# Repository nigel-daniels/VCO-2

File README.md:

# VCO 2

This VCO based on the work of  LMNC [performance VCO](https://www.lookmumnocomputer.com/1222-performance-vco). I've swapped out the built in tuner for a sine wave generator based on the Henry Thomas design. I also expanded the octave range by one and enabled hard/soft sync selection. Finally I've set the gain on the output Op-Amps so that everything is around 9-10V out. Why drop the tuner? Well, I'm unlikely to go performing and I was thinking I'll just build a single tuning module to take advantage of the control panel trim pots.

This module is verified and you can check it out working [here](https://bleepsnbloops.com/?p=62). The module draws +12V 48mA and -12V 21mA (+/-5mA). 

There are a couple of folders included, these contain footprints I used for the switches, import these as project specific items. There is also a JLCPCB folder for the fabrication files of the PCB, I used [JLCPCB](https://jlcpcb.com) for producing this complex board. The PCB design is my own.

I hope you find this useful, and a huge thanks to the LMNC site for some inspiration to do this version of a VCO, also to the lovely people at OnChip Systems (nee [Curtis Electromusic](https://www.curtiselectromusic.com)) who still manufacture and supply the CEM3340. I tracked them down here in San Jose to buy from the source ;)

## Calibration

### Set the reference voltage
Using the test points on the back of the module connect a multimeter in DC mode to GND (`TP22`) and `TP1` for the 5V reference. Use the trimpot next to  `TP1` to tune the voltage to read 5V.

### Shape the sine wave
Now connect an oscilloscope to the sine wave output and use the the other two trimpots to ensure the output sine wave has a good sinusoidal shape. The upper trimpot sets the roundness of the wave and the lower trimpot sets the offset.

## Tuning
On the front panel are three trimpots used to keep the module in tune. For this you'll need a tuner, I just use an app called `Tuner` on my phone. Also fire up the module where you plan to use it an leave it running for about half an hour so it settles to the ambient temperature of your location (this is especially important if you just moved the synth to a new location).
1. First use the `Course` trimpot to get the octave selector covering the sort of range you want.
2. Now use the `Track` trimpot to ensure that each selection on the octave selector is one octave apart from the adjacent options.
3. Once everything is one octave appart you can use the `Course` trimpot to adjust everything to be on a specific note. You may need to iterate these steps until it is all stable.

The `HF Trk` or High Frequency Track can be used in the same way as the `Track` trimpot but is for tuning to high frequencies.

## Test Points

The rear of the module has several test points that can be used with an oscilloscope or multi-meter (q.v.) to calibrate and test the module. These are:

| TP# | Measures | Example | Notes |
| --- | --- | --- | --- |
| 22 | Gnd | | Connect multi-meter or oscilloscope ground here |
| 1 | +5V ref | 5.0V | Set to +5V for the octave selection |
| 2 | Sqr |  | Measure the square wave output. |
| 3 | Saw |  | Measure the ramp wave output. Note this shows a slight clip at the peak. |
| 4 | Tri |  | Measure the triange wave output. |
| 5 | Sin |  | Measure the sine wave output. |

> Nigel Daniels 2026  
> https://bleepsnbloops.com  
> Released under the CERN Open Hardware Licence Version 2 - Strongly Reciprocal

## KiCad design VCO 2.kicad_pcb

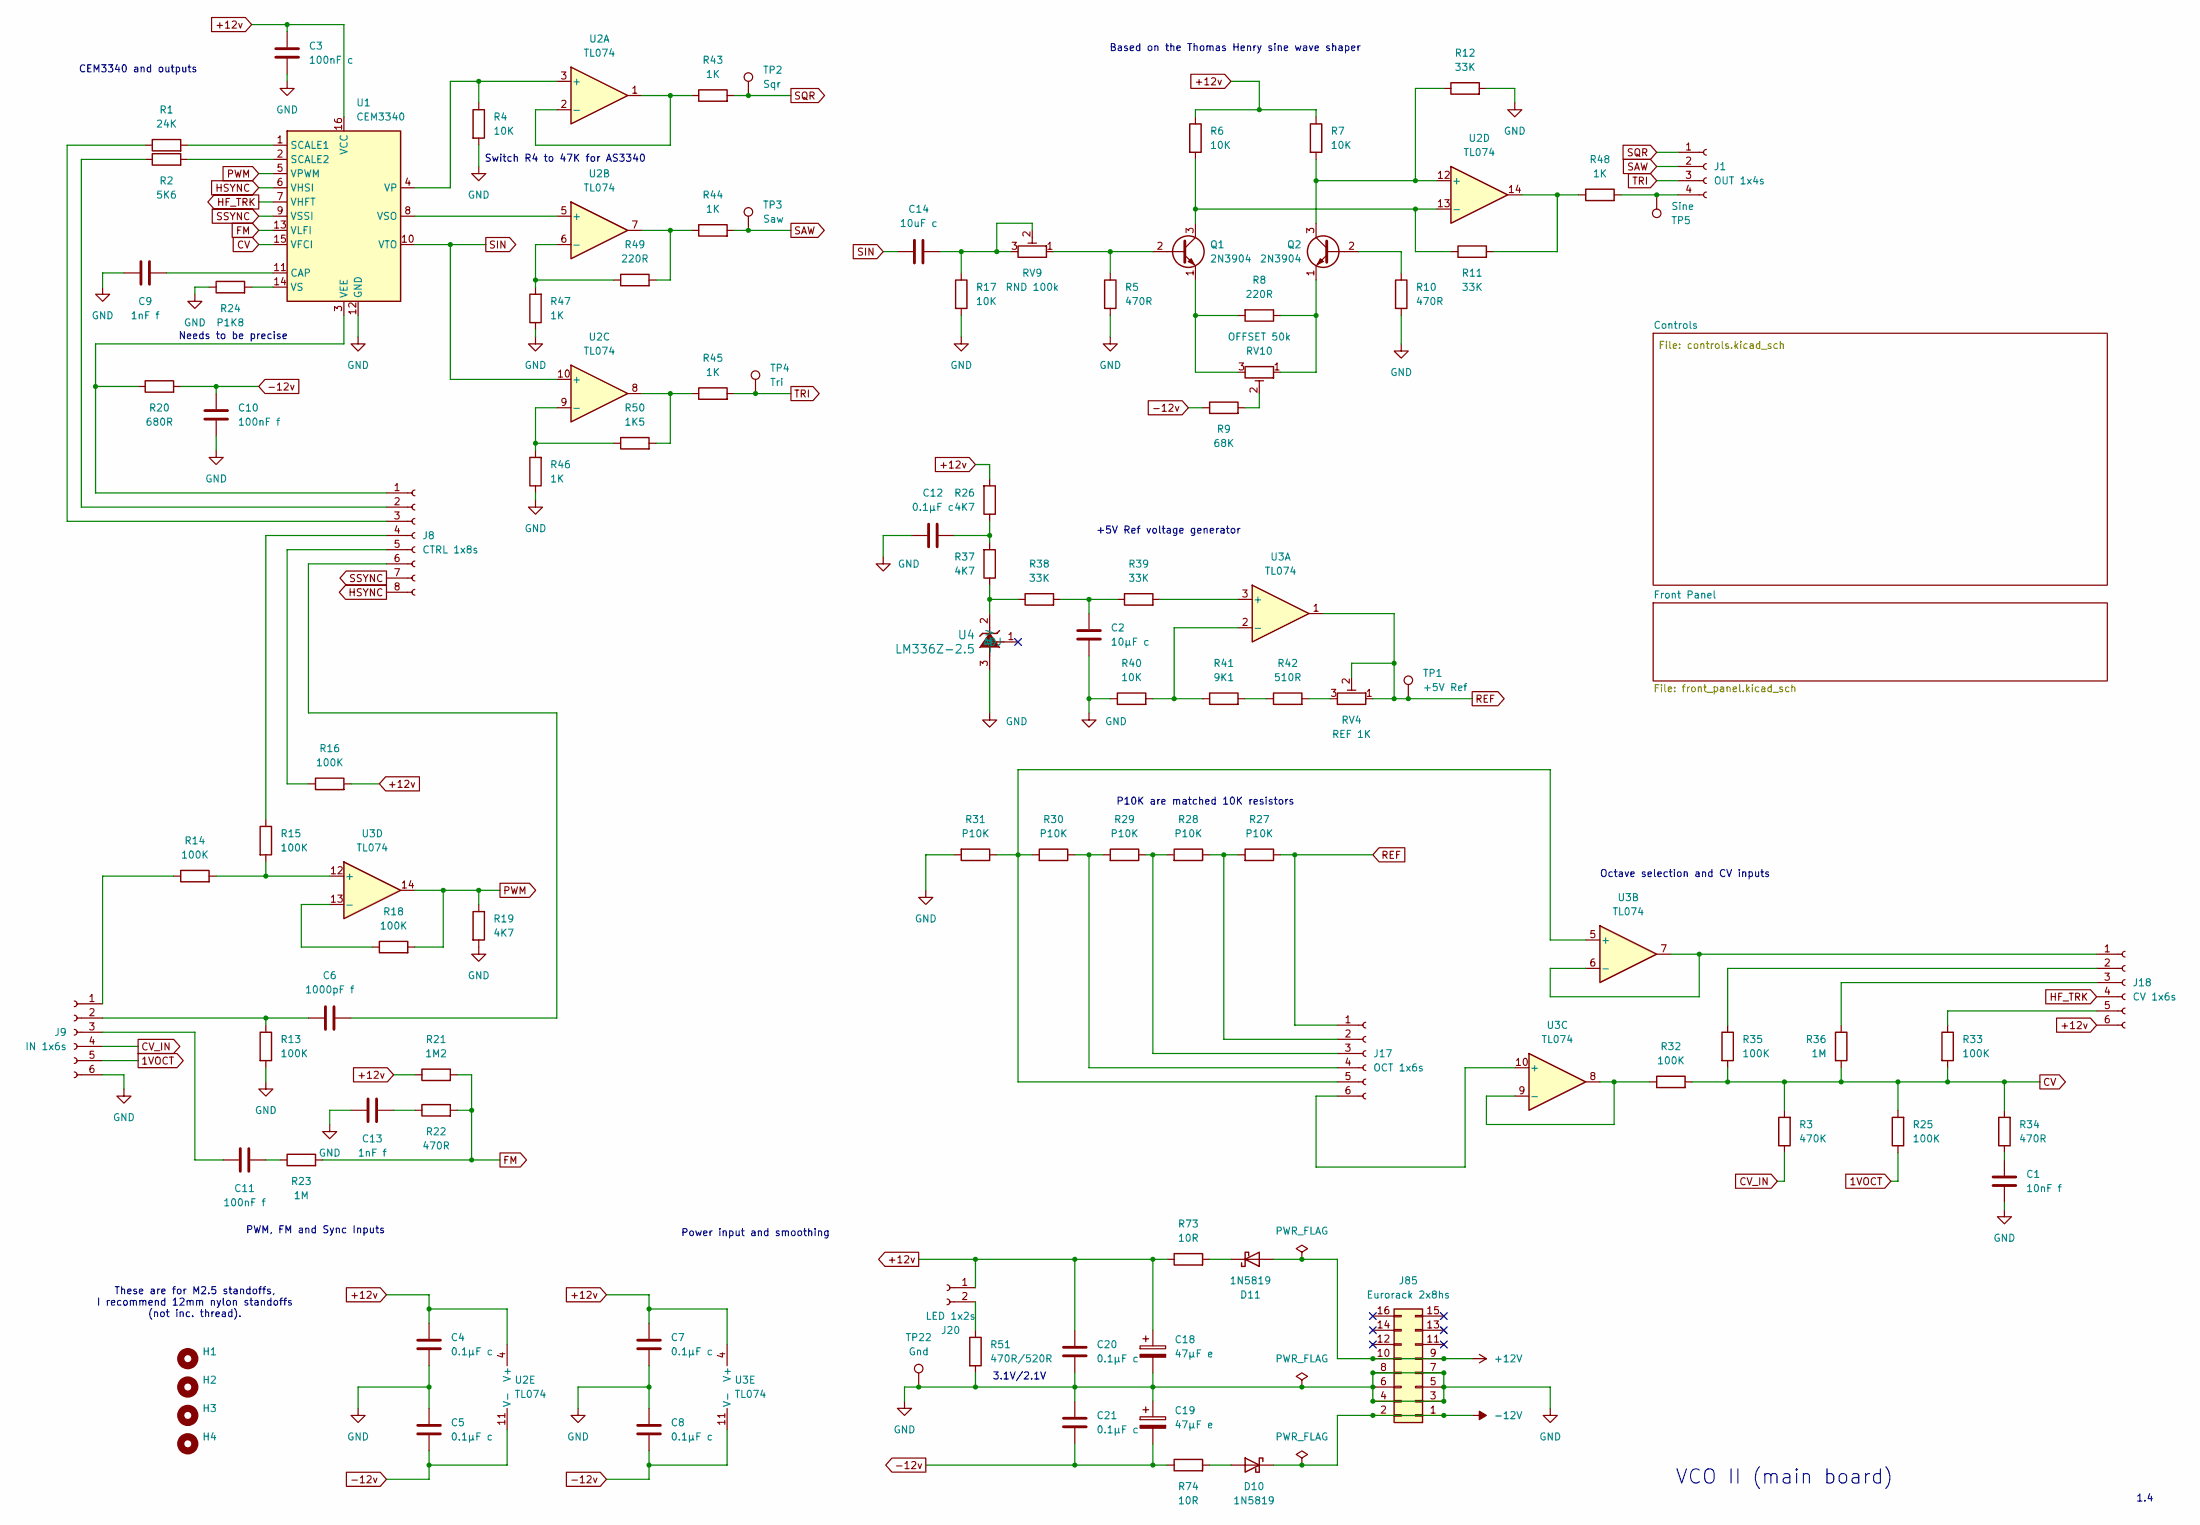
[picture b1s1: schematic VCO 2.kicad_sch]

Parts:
C1: 10nF f; C_Rect_L7.2mm_W2.5mm_P5.00mm
C2: 10μF c; C_Disc_D4.7mm_W2.5mm_P5.00mm
C3: 100nF c; C_Disc_D4.7mm_W2.5mm_P5.00mm
C4, C5, C7, C8, C12, C20, C21: 0.1μF c; C_Disc_D4.7mm_W2.5mm_P5.00mm
C6: 1000pF f; C_Rect_L7.2mm_W2.5mm_P5.00mm
C9, C13: 1nF f; C_Rect_L7.2mm_W2.5mm_P5.00mm
C10, C11: 100nF f; C_Rect_L7.2mm_W2.5mm_P5.00mm
C14: 10uF c; C_Disc_D4.7mm_W2.5mm_P5.00mm
C18, C19: 47μF e; CP_Radial_D5.0mm_P2.50mm
D10, D11: 1N5819; D_DO-41_SOD81_P10.16mm_Horizontal
H1, H2, H3, H4: MountingHole_2.7mm_M2.5
J1: OUT 1x4s; PinSocket_1x04_P2.54mm_Vertical
J8: CTRL 1x8s; PinSocket_1x08_P2.54mm_Vertical
J9: IN 1x6s; PinSocket_1x06_P2.54mm_Vertical
J17: OCT 1x6s; PinSocket_1x06_P2.54mm_Vertical
J18: CV 1x6s; PinSocket_1x06_P2.54mm_Vertical
J20: LED 1x2s; PinSocket_1x02_P2.54mm_Vertical
J85: Eurorack 2x8hs; PinHeader_2x08_P2.54mm_Vertical
Q1, Q2: 2N3904; TO-92_Inline_Wide
R1: 24K; R_Axial_DIN0204_L3.6mm_D1.6mm_P7.62mm_Horizontal
R2: 5K6; R_Axial_DIN0204_L3.6mm_D1.6mm_P2.54mm_Vertical
R3: 470K; R_Axial_DIN0204_L3.6mm_D1.6mm_P7.62mm_Horizontal
R4, R7, R17, R40: 10K; R_Axial_DIN0204_L3.6mm_D1.6mm_P2.54mm_Vertical
R5, R10, R34: 470R; R_Axial_DIN0204_L3.6mm_D1.6mm_P2.54mm_Vertical
R6: 10K; R_Axial_DIN0204_L3.6mm_D1.6mm_P7.62mm_Horizontal
R8, R49: 220R; R_Axial_DIN0204_L3.6mm_D1.6mm_P2.54mm_Vertical
R9: 68K; R_Axial_DIN0204_L3.6mm_D1.6mm_P2.54mm_Vertical
R11, R12, R38, R39: 33K; R_Axial_DIN0204_L3.6mm_D1.6mm_P2.54mm_Vertical
R13, R14, R15, R16, R18, R33, R35: 100K; R_Axial_DIN0204_L3.6mm_D1.6mm_P2.54mm_Vertical
R19, R26, R37: 4K7; R_Axial_DIN0204_L3.6mm_D1.6mm_P2.54mm_Vertical
R20: 680R; R_Axial_DIN0204_L3.6mm_D1.6mm_P2.54mm_Vertical
R21: 1M2; R_Axial_DIN0204_L3.6mm_D1.6mm_P2.54mm_Vertical
R22: 470R; R_Axial_DIN0204_L3.6mm_D1.6mm_P7.62mm_Horizontal
R23: 1M; R_Axial_DIN0204_L3.6mm_D1.6mm_P7.62mm_Horizontal
R24: P1K8; R_Axial_DIN0204_L3.6mm_D1.6mm_P2.54mm_Vertical
R25, R32: 100K; R_Axial_DIN0204_L3.6mm_D1.6mm_P7.62mm_Horizontal
R27, R28, R29, R30, R31: P10K; R_Axial_DIN0204_L3.6mm_D1.6mm_P2.54mm_Vertical
R36: 1M; R_Axial_DIN0204_L3.6mm_D1.6mm_P2.54mm_Vertical
R41: 9K1; R_Axial_DIN0204_L3.6mm_D1.6mm_P2.54mm_Vertical
R42: 510R; R_Axial_DIN0204_L3.6mm_D1.6mm_P2.54mm_Vertical
R43, R44, R45, R46, R47: 1K; R_Axial_DIN0204_L3.6mm_D1.6mm_P2.54mm_Vertical
R48: 1K; R_Axial_DIN0204_L3.6mm_D1.6mm_P7.62mm_Horizontal
R50: 1K5; R_Axial_DIN0204_L3.6mm_D1.6mm_P2.54mm_Vertical
R51: 470R/520R; R_Axial_DIN0204_L3.6mm_D1.6mm_P2.54mm_Vertical
R73, R74: 10R; R_Axial_DIN0204_L3.6mm_D1.6mm_P2.54mm_Vertical
RV4: REF 1K; Potentiometer_Bourns_3296W_Vertical
RV9: RND 100k; Potentiometer_Bourns_3296W_Vertical
RV10: OFFSET 50k; Potentiometer_Bourns_3296W_Vertical
TP1: +5V Ref; TestPoint_Loop_D2.50mm_Drill1.0mm
TP2: Sqr; TestPoint_Loop_D2.50mm_Drill1.0mm
TP3: Saw; TestPoint_Loop_D2.50mm_Drill1.0mm
TP4: Tri; TestPoint_Loop_D2.50mm_Drill1.0mm
TP5: Sine; TestPoint_Loop_D2.50mm_Drill1.0mm
TP22: Gnd; TestPoint_Loop_D2.50mm_Drill1.0mm
U1: CEM3340; DIP-16_W7.62mm
U2, U3: TL074; DIP-14_W7.62mm
U4: LM336Z-2.5; Z03A

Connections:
1VOCT: J9.5, R25.1
+12V: D11.2 (A), J85.9, J85.10
+12v: C3.1, C4.1, C7.1, C18.1, C20.1, J18.6, J20.1, R6.1, R7.1, R16.2, R21.1, R26.2, R73.1, U1.16 (VCC), U2.4 (V+), U3.4 (V+)
-12V: D10.1 (K), J85.1, J85.2
-12v: C5.2, C8.2, C10.2, C19.2, C21.2, R9.1, R20.2, R74.1, U2.11 (V-), U3.11 (V-)
CV: R3.2, R25.2, R32.2, R33.2, R34.2, R35.2, R36.2, U1.15 (VFCI)
CV_IN: J9.4, R3.1
FM: R21.2, R22.2, R23.2, U1.13 (VLFI)
GND: C1.2, C2.2, C3.2, C4.2, C5.1, C7.2, C8.1, C9.2, C10.1, C12.2, C13.1, C18.2, C19.1, C20.2, C21.1, J9.6, J85.3, J85.4, J85.5, J85.6, J85.7, J85.8, R4.2, R5.2, R10.2, R12.2, R13.2, R17.2, R19.2, R24.1, R31.2, R40.1, R46.1, R47.1, R51.2, TP22.1 (1_1), U1.12 (GND), U4.3 (-V); also elsewhere on the board
HF_TRK: J18.4, U1.7 (VHFT)
HSYNC: J8.8, U1.6 (VHSI)
unnamed: C1.1, R34.1
unnamed: C2.1, R38.2, R39.1
unnamed: C11.2, R23.1
unnamed: C12.1, R26.1, R37.2
unnamed: C13.2, R22.1
unnamed: C14.1, R17.1, RV9.2, RV9.3
unnamed: D10.2 (A), R74.2
unnamed: D11.1 (K), R73.2
unnamed: J1.4, R48.2, TP5.1 (1_1)
unnamed: J8.1, R20.1, U1.3 (VEE)
unnamed: J8.2, R2.1
unnamed: J8.3, R1.1
unnamed: J8.4, R15.1
unnamed: J8.5, R16.1
unnamed: C6.1, J8.6
unnamed: J9.1, R14.1
unnamed: C6.2, J9.2, R13.1
unnamed: C11.1, J9.3
unnamed: J17.2, R27.2, R28.1
unnamed: J17.3, R28.2, R29.1
unnamed: J17.4, R29.2, R30.1
unnamed: J17.5, R30.2, R31.1, U3.5 (+)
unnamed: J17.6, U3.10 (+)
unnamed: J18.1, U3.6 (-), U3.7
unnamed: J18.2, R35.1
unnamed: J18.3, R36.1
unnamed: J18.5, R33.1
unnamed: J20.2, R51.1
unnamed: Q1.2 (B), R5.1, RV9.1
unnamed: Q1.3 (C), R6.2, R11.1, U2.13 (-)
unnamed: Q1.1 (E), R8.2, RV10.3
unnamed: Q2.2 (B), R10.1
unnamed: Q2.3 (C), R7.2, R12.1, U2.12 (+)
unnamed: Q2.1 (E), R8.1, RV10.1
unnamed: R9.2, RV10.2
unnamed: R11.2, R48.1, U2.14
unnamed: R41.2, R42.1
unnamed: R42.2, RV4.3
unnamed: R44.1, R49.2, U2.7
unnamed: R45.1, R50.2, U2.8
unnamed: C9.1, U1.11 (CAP)
unnamed: R1.2, U1.1 (SCALE1)
unnamed: R2.2, U1.2 (SCALE2)
unnamed: R4.1, U1.4 (VP), U2.3 (+)
unnamed: R24.2, U1.14 (VS)
unnamed: U1.8 (VSO), U2.5 (+)
unnamed: R43.1, U2.1, U2.2 (-)
unnamed: R47.2, R49.1, U2.6 (-)
unnamed: R46.2, R50.1, U2.9 (-)
unnamed: R39.2, U3.3 (+)
unnamed: R40.2, R41.1, U3.2 (-)
unnamed: R32.1, U3.8, U3.9 (-)
unnamed: R14.2, R15.2, U3.12 (+)
unnamed: R18.1, U3.13 (-)
unnamed: R37.1, R38.1, U4.2 (+V)
PWM: R18.2, R19.1, U1.5 (VPWM), U3.14
REF: J17.1, R27.1, RV4.1, RV4.2, TP1.1 (1_1), U3.1
SAW: J1.2, R44.2, TP3.1 (1_1)
SIN: C14.2, U1.10 (VTO), U2.10 (+)
SQR: J1.1, R43.2, TP2.1 (1_1)
SSYNC: J8.7, U1.9 (VSSI)
TRI: J1.3, R45.2, TP4.1 (1_1)

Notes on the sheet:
3.1V/2.1V
CEM3340 and outputs
Needs to be precise
Switch R4 to 47K for AS3340
+5V Ref voltage generator
These are for M2.5 standoffs, I recommend 12mm nylon standoffs (not inc. thread).
P10K are matched 10K resistors
Based on the Thomas Henry sine wave shaper
1.4
PWM, FM and Sync Inputs
Power input and smoothing
VCO II (main board)
Octave selection and CV inputs

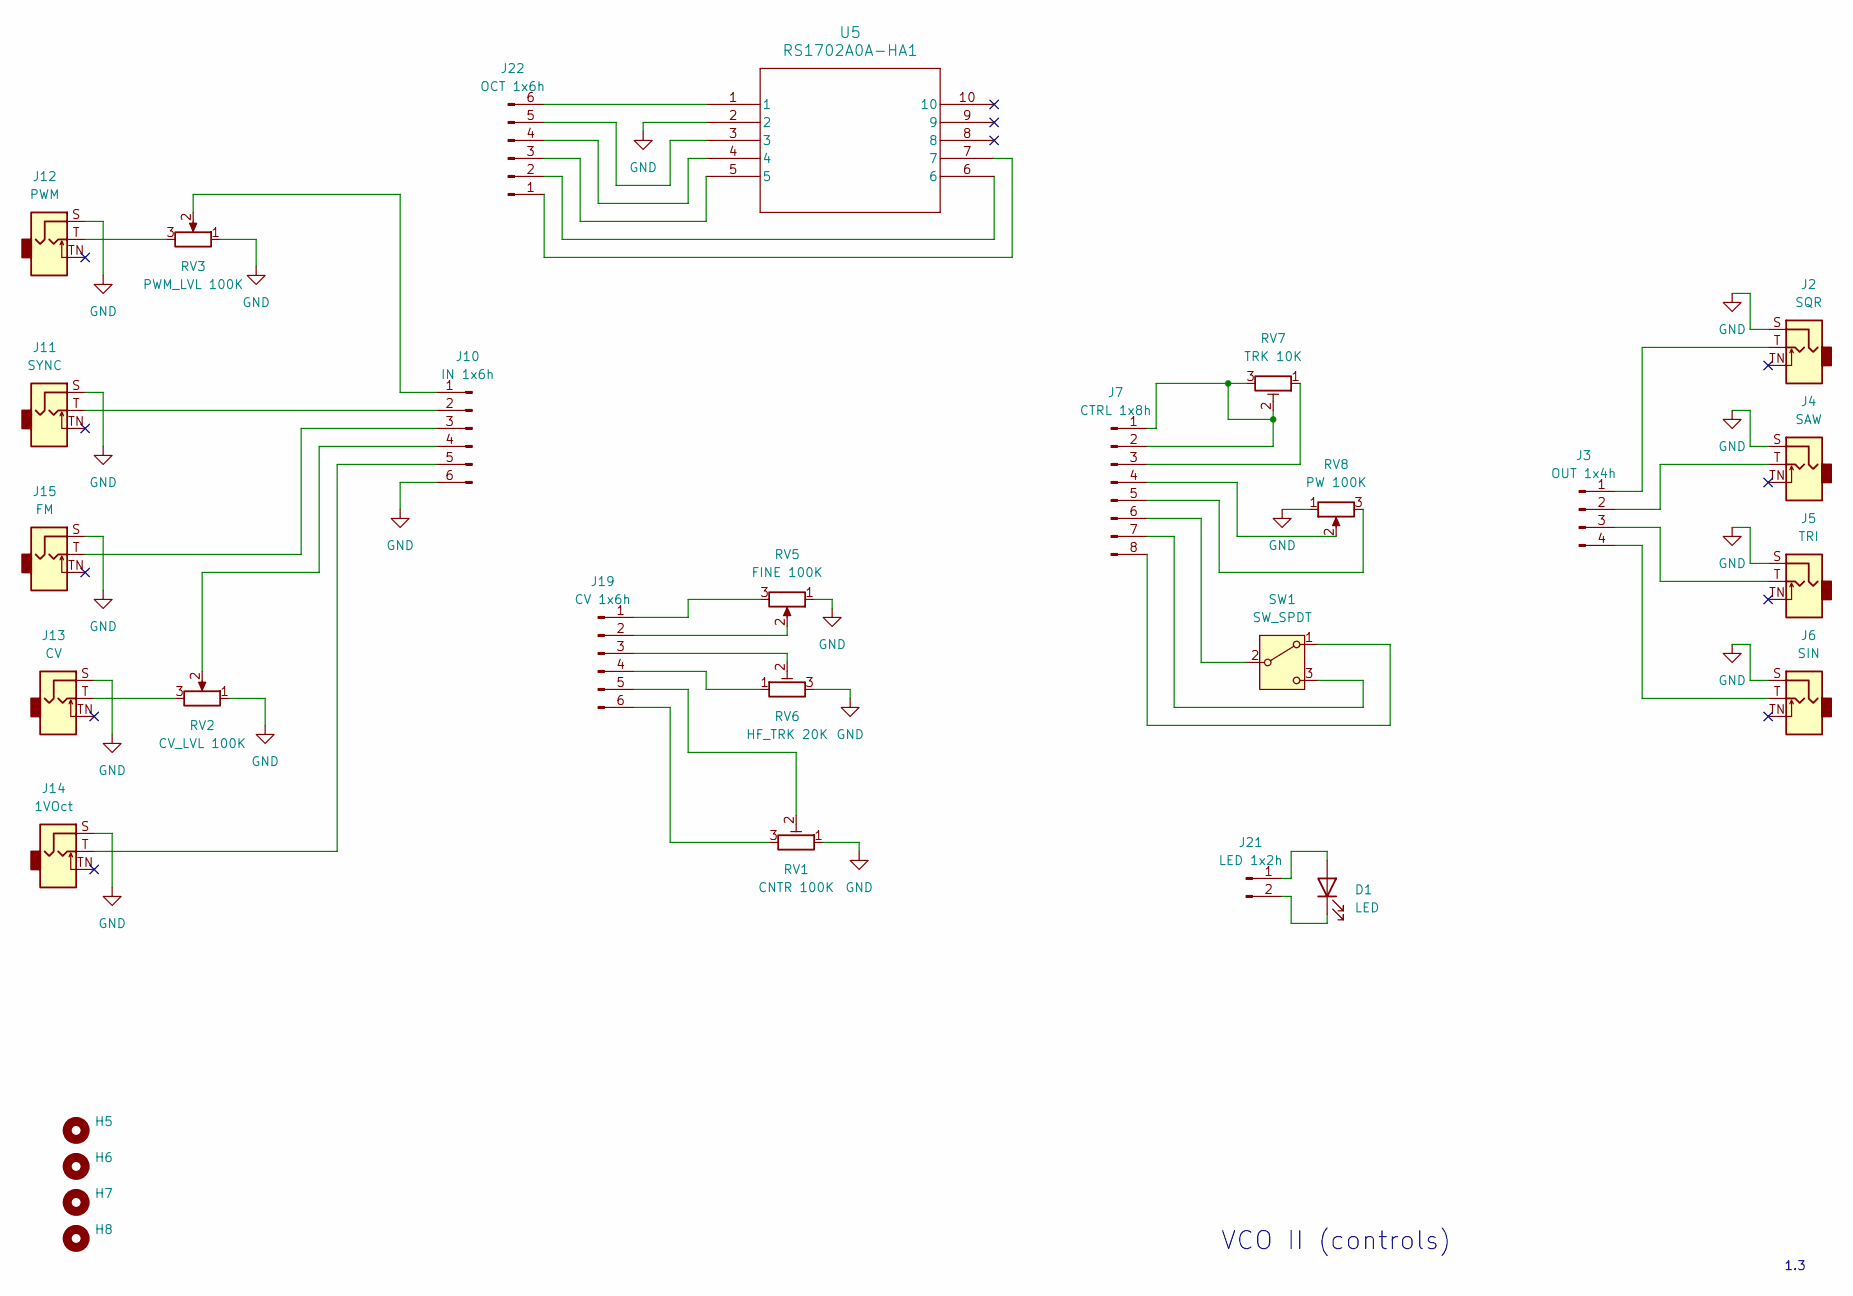
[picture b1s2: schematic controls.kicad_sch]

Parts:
D1: LED; LED_D3.0mm_FlatTop
H5, H6, H7, H8: MountingHole_2.7mm_M2.5
J2: SQR; Jack_3.5mm_QingPu_WQP-PJ398SM_Vertical_CircularHoles
J3: OUT 1x4h; PinHeader_1x04_P2.54mm_Vertical
J4: SAW; Jack_3.5mm_QingPu_WQP-PJ398SM_Vertical_CircularHoles
J5: TRI; Jack_3.5mm_QingPu_WQP-PJ398SM_Vertical_CircularHoles
J6: SIN; Jack_3.5mm_QingPu_WQP-PJ398SM_Vertical_CircularHoles
J7: CTRL 1x8h; PinHeader_1x08_P2.54mm_Vertical
J10: IN 1x6h; PinHeader_1x06_P2.54mm_Vertical
J11: SYNC; Jack_3.5mm_QingPu_WQP-PJ398SM_Vertical_CircularHoles
J12: PWM; Jack_3.5mm_QingPu_WQP-PJ398SM_Vertical_CircularHoles
J13: CV; Jack_3.5mm_QingPu_WQP-PJ398SM_Vertical_CircularHoles
J14: 1VOct; Jack_3.5mm_QingPu_WQP-PJ398SM_Vertical_CircularHoles
J15: FM; Jack_3.5mm_QingPu_WQP-PJ398SM_Vertical_CircularHoles
J19: CV 1x6h; PinHeader_1x06_P2.54mm_Vertical
J21: LED 1x2h; PinHeader_1x02_P2.54mm_Vertical
J22: OCT 1x6h; PinHeader_1x06_P2.54mm_Vertical
RV1: CNTR 100K; Potentiometer_Bourns_3296W_Vertical
RV2: CV_LVL 100K; Potentiometer_Alps_RK09L_Single_Vertical
RV3: PWM_LVL 100K; Potentiometer_Alps_RK09L_Single_Vertical
RV5: FINE 100K; Potentiometer_Alps_RK09L_Single_Vertical
RV6: HF_TRK 20K; Potentiometer_Bourns_3296W_Vertical
RV7: TRK 10K; Potentiometer_Bourns_3296W_Vertical
RV8: PW 100K; Potentiometer_Alps_RK09L_Single_Vertical
SW1: SW_SPDT; Sub-miniture SPDT
U5: RS1702A0A-HA1; rotary-6-way-sw

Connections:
GND: J2.S, J4.S, J5.S, J6.S, J10.6, J11.S, J12.S, J13.S, J14.S, J15.S, RV1.1, RV2.1, RV3.1, RV5.1, RV6.3, RV8.1, U5.2; also elsewhere on the board
unnamed: D1.2 (A), J21.1
unnamed: D1.1 (K), J21.2
unnamed: J2.T, J3.1
unnamed: J3.2, J4.T
unnamed: J3.3, J5.T
unnamed: J3.4, J6.T
unnamed: J7.1, J7.2, RV7.2, RV7.3
unnamed: J7.3, RV7.1
unnamed: J7.4, RV8.2
unnamed: J7.5, RV8.3
unnamed: J7.6, SW1.2 (B)
unnamed: J7.7, SW1.3 (C)
unnamed: J7.8, SW1.1 (A)
unnamed: J10.1, RV3.2
unnamed: J10.2, J11.T
unnamed: J10.3, J15.T
unnamed: J10.4, RV2.2
unnamed: J10.5, J14.T
unnamed: J12.T, RV3.3
unnamed: J13.T, RV2.3
unnamed: J19.1, RV5.3
unnamed: J19.2, RV5.2
unnamed: J19.3, RV6.2
unnamed: J19.4, RV6.1
unnamed: J19.5, RV1.2
unnamed: J19.6, RV1.3
unnamed: J22.1, U5.7
unnamed: J22.2, U5.6
unnamed: J22.3, U5.5
unnamed: J22.4, U5.4
unnamed: J22.5, U5.3
unnamed: J22.6, U5.1

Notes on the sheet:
VCO II (controls)
1.3

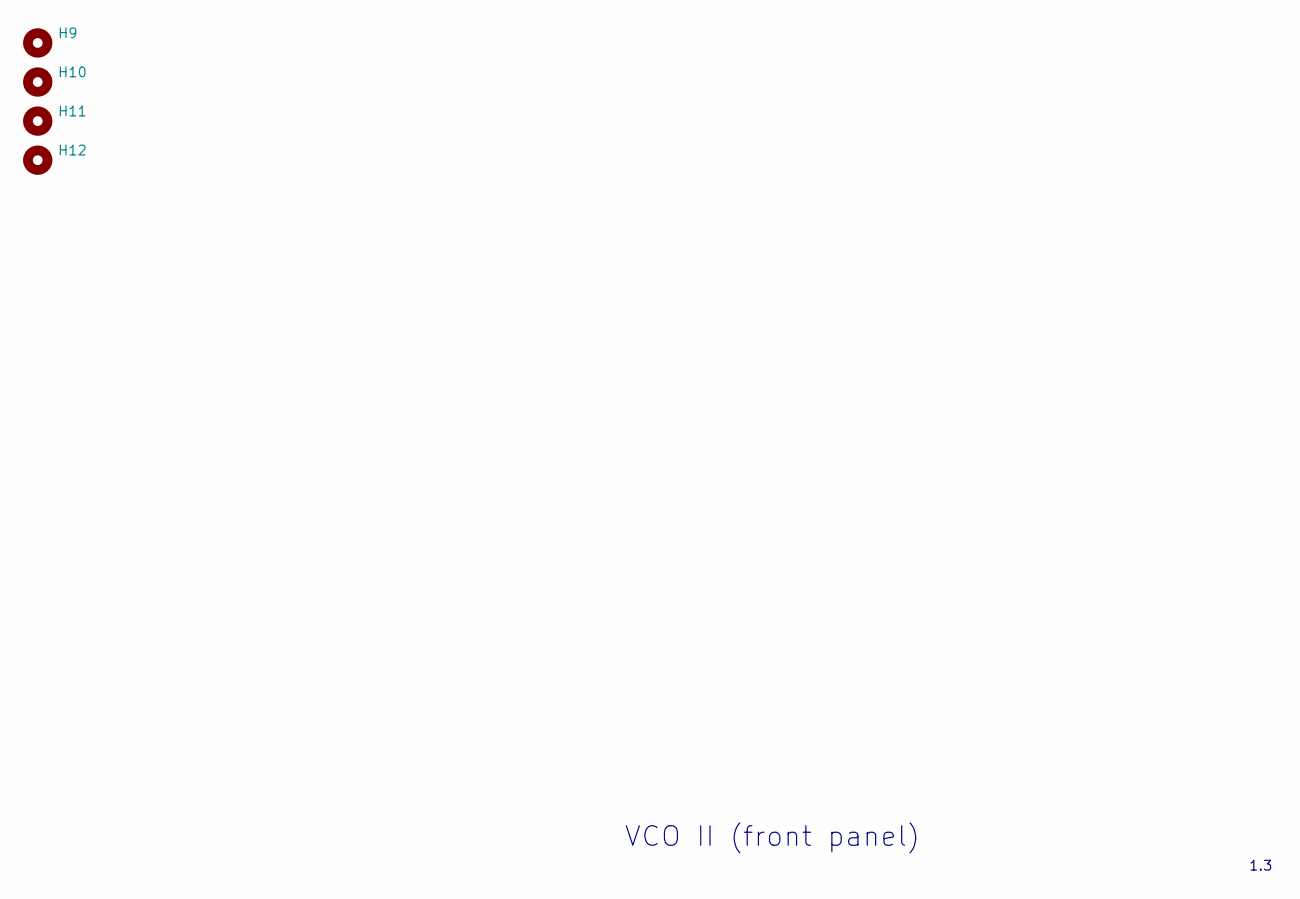
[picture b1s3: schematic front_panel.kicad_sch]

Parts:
H9, H10, H11, H12: MountingHole_3.2mm_M3

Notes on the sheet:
VCO II (front panel)
1.3

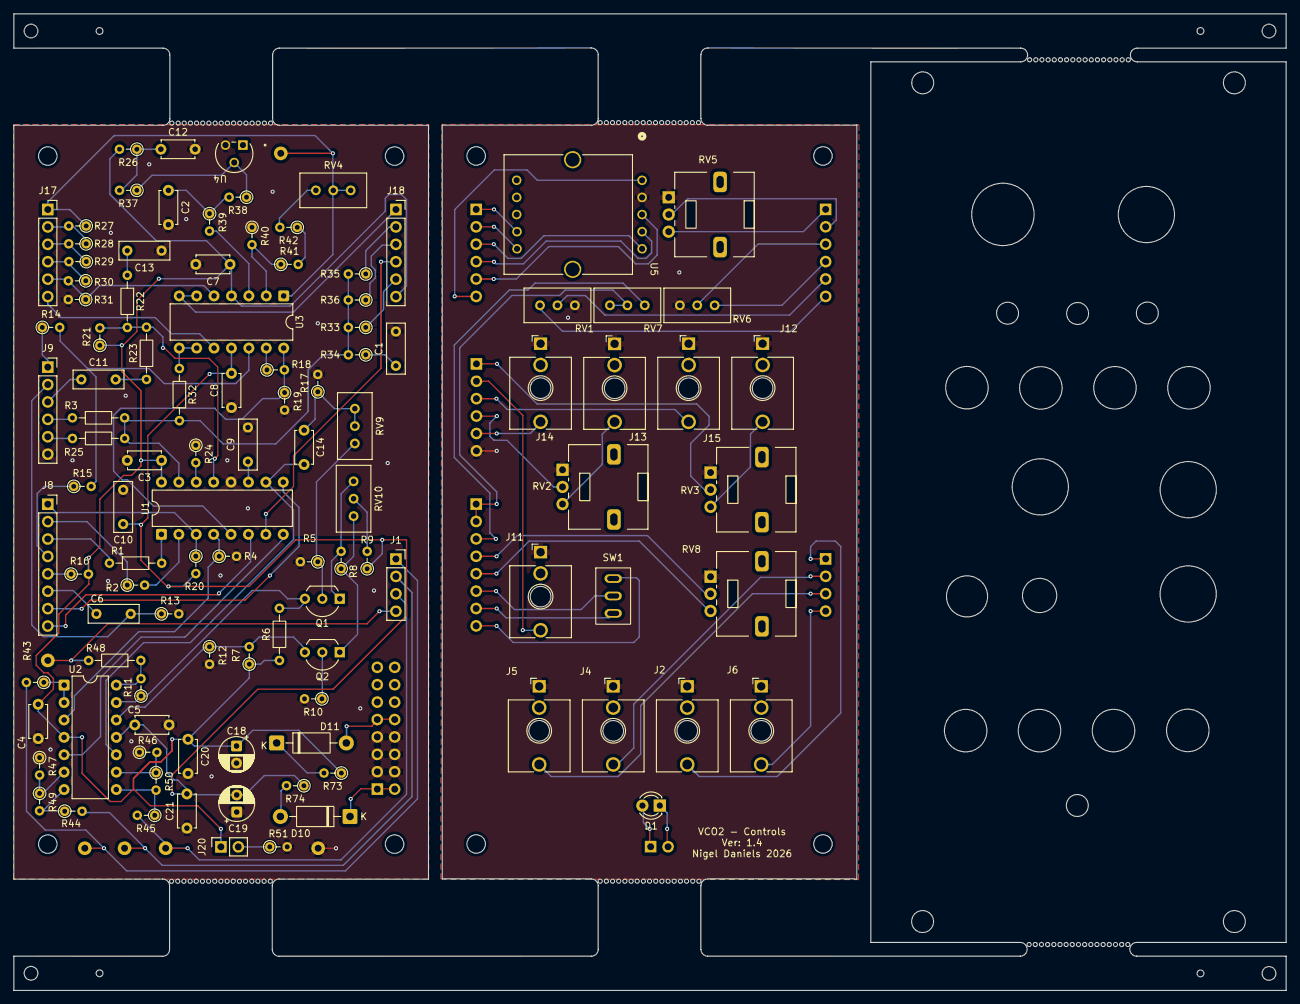
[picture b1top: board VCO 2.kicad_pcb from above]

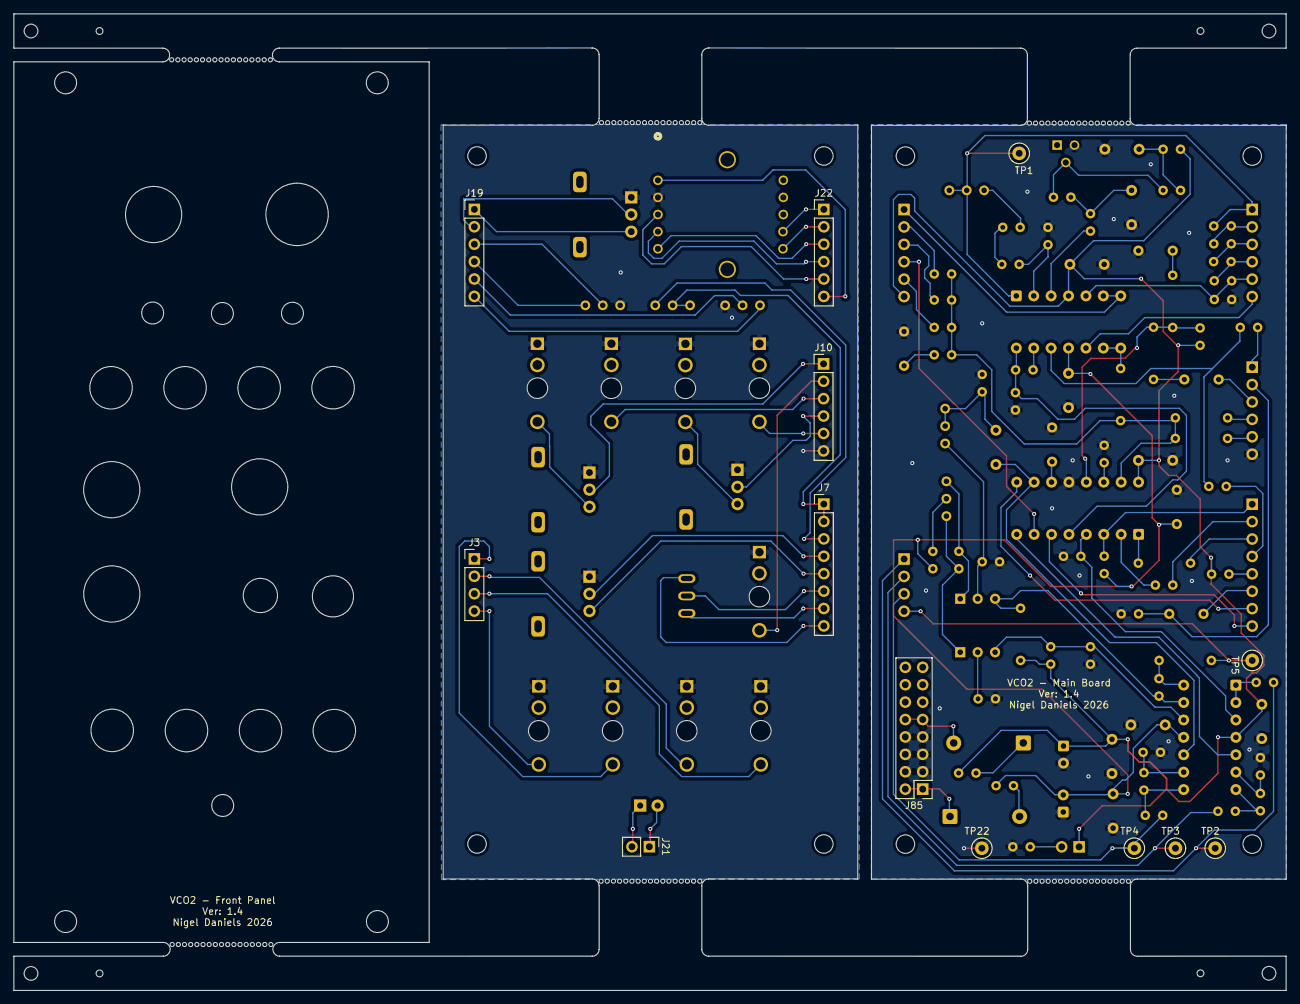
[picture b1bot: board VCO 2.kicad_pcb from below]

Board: 2 copper layers, 185.6 x 142.4 mm, 132 parts (13 on the bottom side), 105 nets.

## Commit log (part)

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2026-02-27 remove backup
2026-02-27 ignore update
2026-02-27 removed ignores
2026-03-01 Added +5v ref supply
2026-03-05 +5V ref update
2026-03-08 Corrected output jack sockets
2026-03-08 Simulated and corrected ref V
2026-03-08 Updated ref design
2026-03-09 Added Falstad CV model
2026-03-09 Created falstad folder
2026-03-11 Updated simulator and corrected trk pot
2026-03-11 Falkstad updates
2026-03-12 Added FM and PWM falstad models
2026-03-12 Updated FM PWM model
2026-03-12 Added sine wave generator model
2026-03-24 Updates to jacks
2026-03-27 Fixed FM sweep
2026-03-27 Falstad sine update
2026-03-27 Sine simulator update
2026-03-27 Added decoupling C and R to prevent MacArches
2026-03-27 Added gain and 1k protection to output and LED, rerouted SIN feed.
2026-03-27 Added images to read me
2026-03-27 Updated readme.
2026-03-27 Updated images and fixed readme.
2026-03-27 fixed readme.
2026-03-27 Moved LED to control board.
2026-03-28 Update README.md
    Pulled PCB remark from old project
2026-03-28 Updated TP names
2026-03-31 Added fp and moved controls
2026-04-02 Designed PCB and generated JLCPCB files
2026-04-02 Panelized design using tab and mouse bites
2026-04-02 Added full panel dimensions
2026-04-02 Read Me updated
2026-04-03 Started FP visuals, corrected SPDT SW footprint.
2026-04-03 Updated switch footprint to use imported footprint
2026-04-04 Version confirmed to production
2026-04-04 FP designs
2026-04-04 Removed unused switch
2026-04-13 Fixed switches, added new FPs and symbols.
2026-04-13 Updated graphics
2026-04-13 Updates for BOM
2026-04-13 Symbol updated
2026-04-13 Consolidated BOM
2026-04-15 Design updates
2026-04-22 Updates to BOM
2026-06-11 Corrected connections for levels and octave switch
2026-06-11 Updated to correct for DRC check and refreshed fab files
2026-06-12 Tweaked routes
2026-06-12 Updated .gitignore
